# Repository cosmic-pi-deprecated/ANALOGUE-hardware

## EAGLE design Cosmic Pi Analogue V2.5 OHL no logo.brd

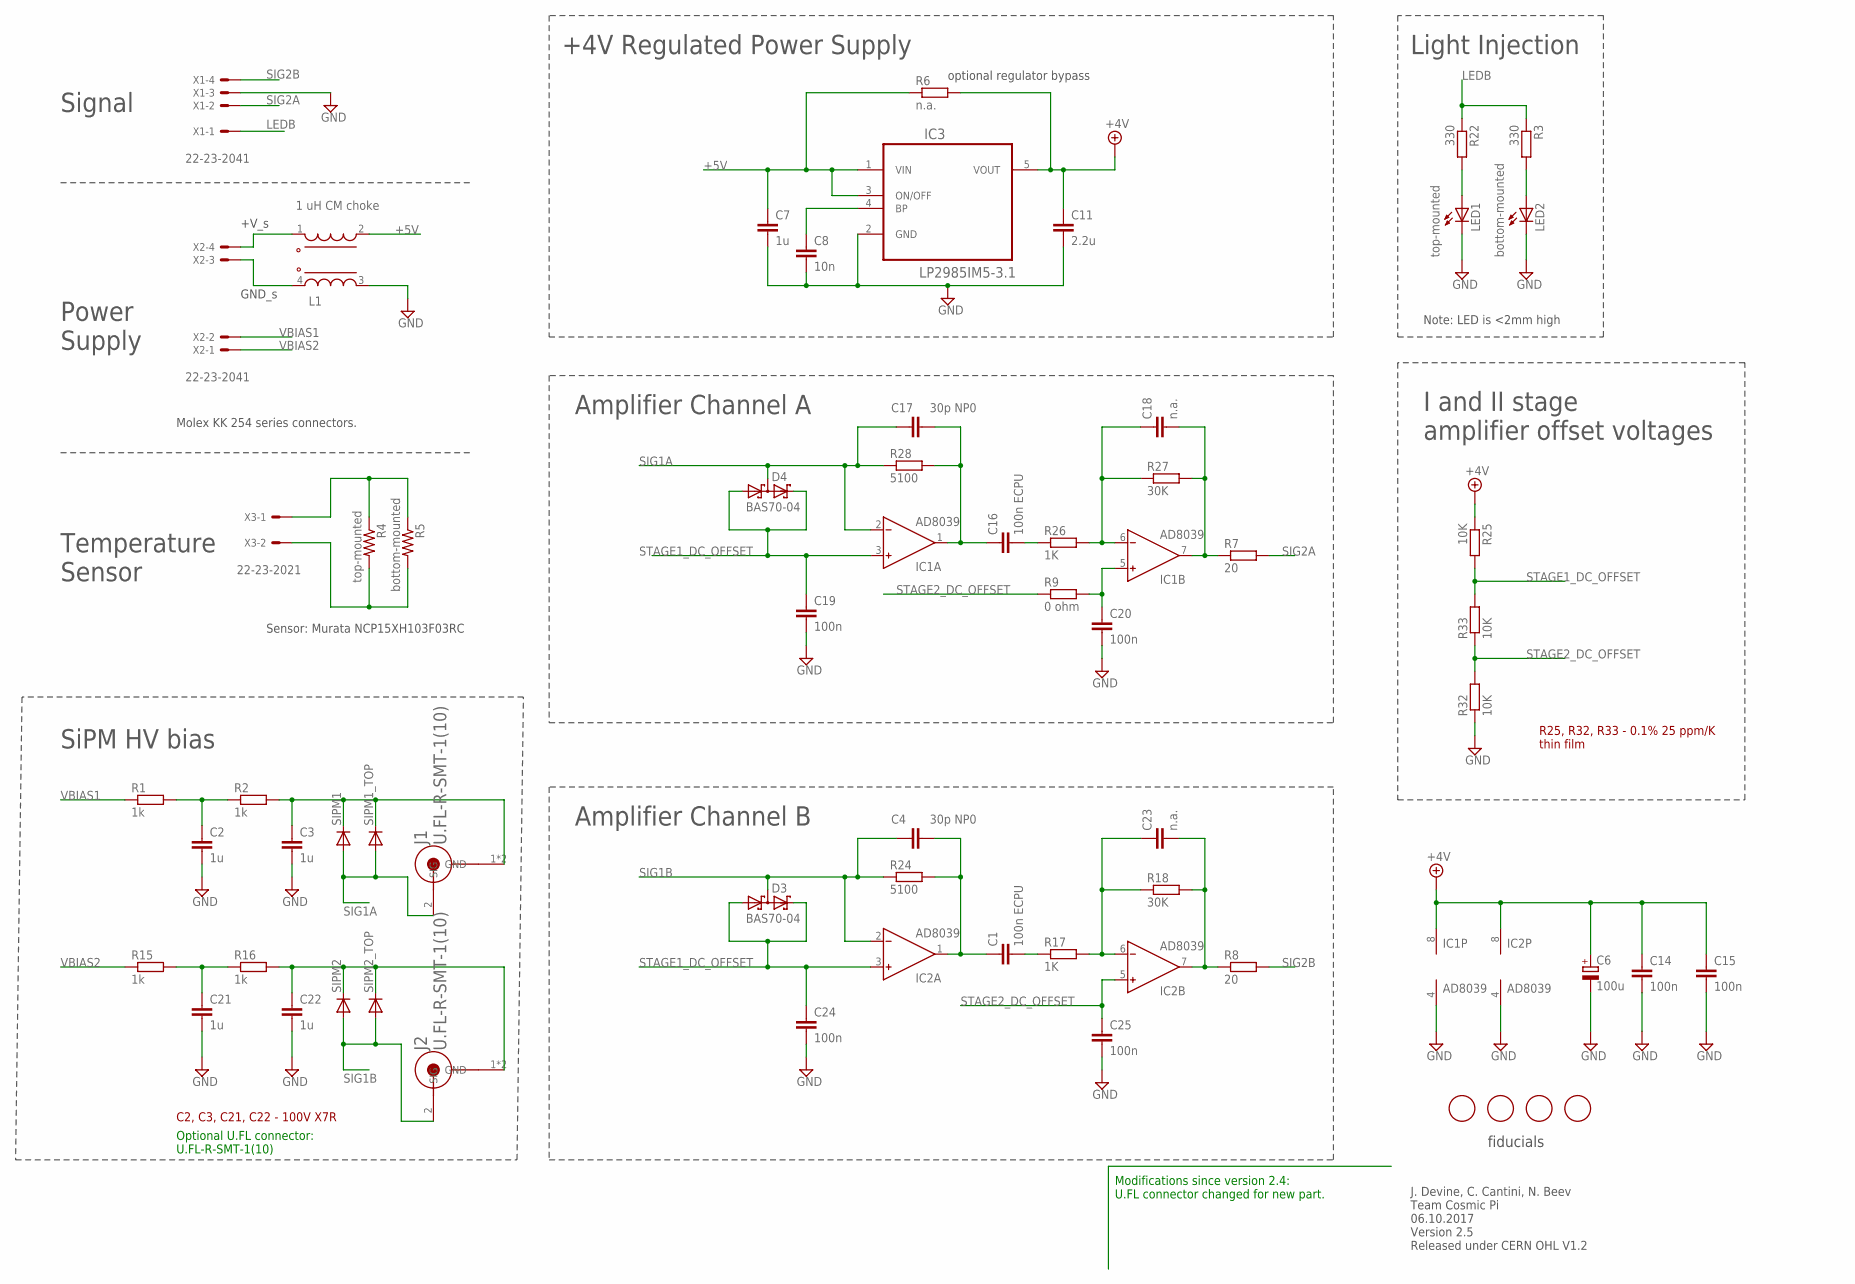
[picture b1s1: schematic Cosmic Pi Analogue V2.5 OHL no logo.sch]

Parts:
C1, C16: 100n ECPU; C0805
C2, C3, C21, C22: 1u; C1206
C4, C17: 30p NP0; C0603
C6: 100u; C/6032-28R
C7: 1u; C0603
C8: 10n; C0603
C11: 2.2u; C0603
C14, C15, C19, C20, C24, C25: 100n; C0603
C18, C23: n.a.; C0603
D3, D4: BAS70-04; SOT23
IC1, IC2: AD8039; SO8
IC3: LP2985IM5-3.1; SOT95P284X120-5N
J1, J2: U.FL-R-SMT-1(10); HRS_U.FL-R-SMT-1(10)
L1: 1 uH CM choke; WE-CNSW_1812
LED1: top-mounted; LED_SML0603
LED2: bottom-mounted; LED_SML0603
R1, R2, R15, R16: 1k; R1206
R3, R22: 330; R0603
R4: top-mounted; R0402
R5: bottom-mounted; R0402
R6: n.a.; R0603
R7, R8: 20; R0603
R9: 0 ohm; R1206
R17, R26: 1K; R0603
R18, R27: 30K; R0603
R24, R28: 5100; R0603
R25, R32, R33: 10K; R0805
SIPM1, SIPM1_TOP, SIPM2, SIPM2_TOP: DIODE-ADVANSID; ASD-NUV3S-P
U$2, U$3, U$4, U$5: FIDUCIAL; FIDUCIAL_1MM
X1, X2: 22-23-2041
X3: 22-23-2021

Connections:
+4V: C6.+, C11.1, C14.1, C15.1, IC1.8 (V+), IC2.8 (V+), IC3.5 (VOUT), R6.2, R25.1
+5V: C7.1, IC3.1 (VIN), IC3.3 (ON/OFF), L1.2 (3), R6.1
GND: C2.2, C3.2, C6.-, C7.2, C8.2, C11.2, C14.2, C15.2, C19.2, C20.2, C21.2, C22.2, C24.2, C25.2, IC1.4 (V-), IC2.4 (V-), IC3.2 (GND), L1.3 (2), LED1.C, LED2.C, R32.1, X1.3
LEDB: R3.1, R22.1, X1.1
unnamed: L1.1 (4), X2.4
unnamed: L1.4 (1), X2.3
unnamed: LED2.A, R3.2
unnamed: C8.1, IC3.4 (BP)
unnamed: C21.1, R15.2, R16.1
unnamed: C18.2, IC1.7 (OUT), R7.1, R27.2
unnamed: C22.1, J2.1 (GND), J2.3 (GND), R16.2, SIPM2.P$1 (C), SIPM2_TOP.P$1 (C)
unnamed: R4.1, R5.1, X3.1
unnamed: C23.2, IC2.7 (OUT), R8.1, R18.2
unnamed: C2.1, R1.2, R2.1
unnamed: R4.2, R5.2, X3.2
unnamed: C20.1, IC1.5 (IN+), R9.2
unnamed: C3.1, J1.1 (GND), J1.3 (GND), R2.2, SIPM1.P$1 (C), SIPM1_TOP.P$1 (C)
unnamed: LED1.A, R22.2
unnamed: C1.1, C4.2, IC2.1 (OUT), R24.2
unnamed: C1.2, R17.1
unnamed: C23.1, IC2.6 (IN-), R17.2, R18.1
unnamed: C16.1, C17.2, IC1.1 (OUT), R28.2
unnamed: C16.2, R26.1
unnamed: C18.1, IC1.6 (IN-), R26.2, R27.1
SIG1A: C17.1, D4.3 (C1A2), IC1.2 (IN-), J1.2 (SIG), R28.1, SIPM1.P$2 (A), SIPM1_TOP.P$2 (A)
SIG1B: C4.1, D3.3 (C1A2), IC2.2 (IN-), J2.2 (SIG), R24.1, SIPM2.P$2 (A), SIPM2_TOP.P$2 (A)
SIG2A: R7.2, X1.2
SIG2B: R8.2, X1.4
STAGE1_DC_OFFSET: C19.1, C24.1, D3.1 (A1), D3.2 (C2), D4.1 (A1), D4.2 (C2), IC1.3 (IN+), IC2.3 (IN+), R25.2, R33.2
STAGE2_DC_OFFSET: C25.1, IC2.5 (IN+), R9.1, R32.2, R33.1
VBIAS1: R1.1, X2.2
VBIAS2: R15.1, X2.1

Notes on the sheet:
J. Devine, C. Cantini, N. Beev Team Cosmic Pi 06.10.2017 Version 2.5 Released under CERN OHL V1.2
Signal
Power Supply
Molex KK 254 series connectors.
Note: LED is <2mm high
+4V Regulated Power Supply
Amplifier Channel A
Amplifier Channel B
SiPM HV bias
Temperature Sensor
optional regulator bypass
+V_s
GND_s
Light Injection
I and II stage amplifier offset voltages
fiducials
Sensor: Murata NCP15XH103F03RC
R25, R32, R33 - 0.1% 25 ppm/K thin film
C2, C3, C21, C22 - 100V X7R
Optional U.FL connector: U.FL-R-SMT-1(10)
Modifications since version 2.4: U.FL connector changed for new part.

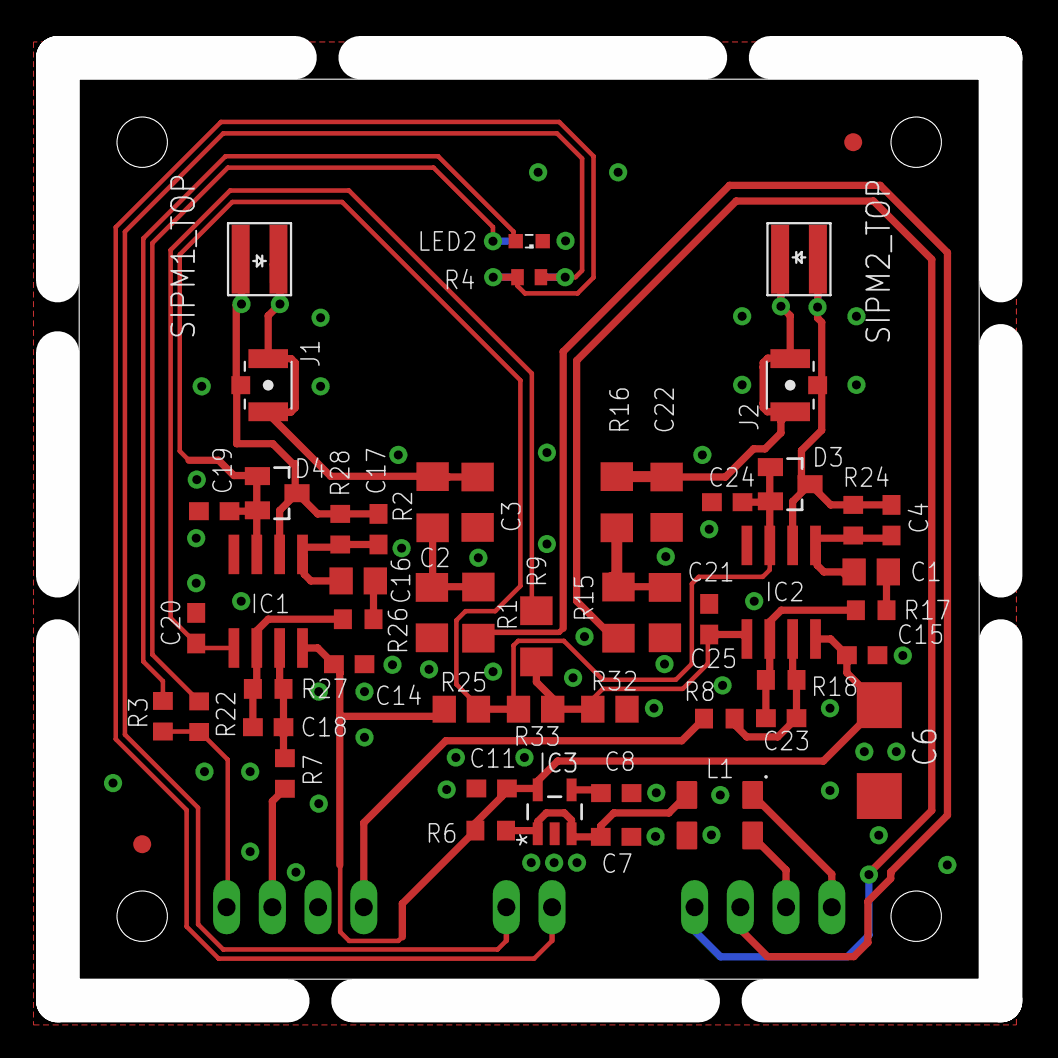
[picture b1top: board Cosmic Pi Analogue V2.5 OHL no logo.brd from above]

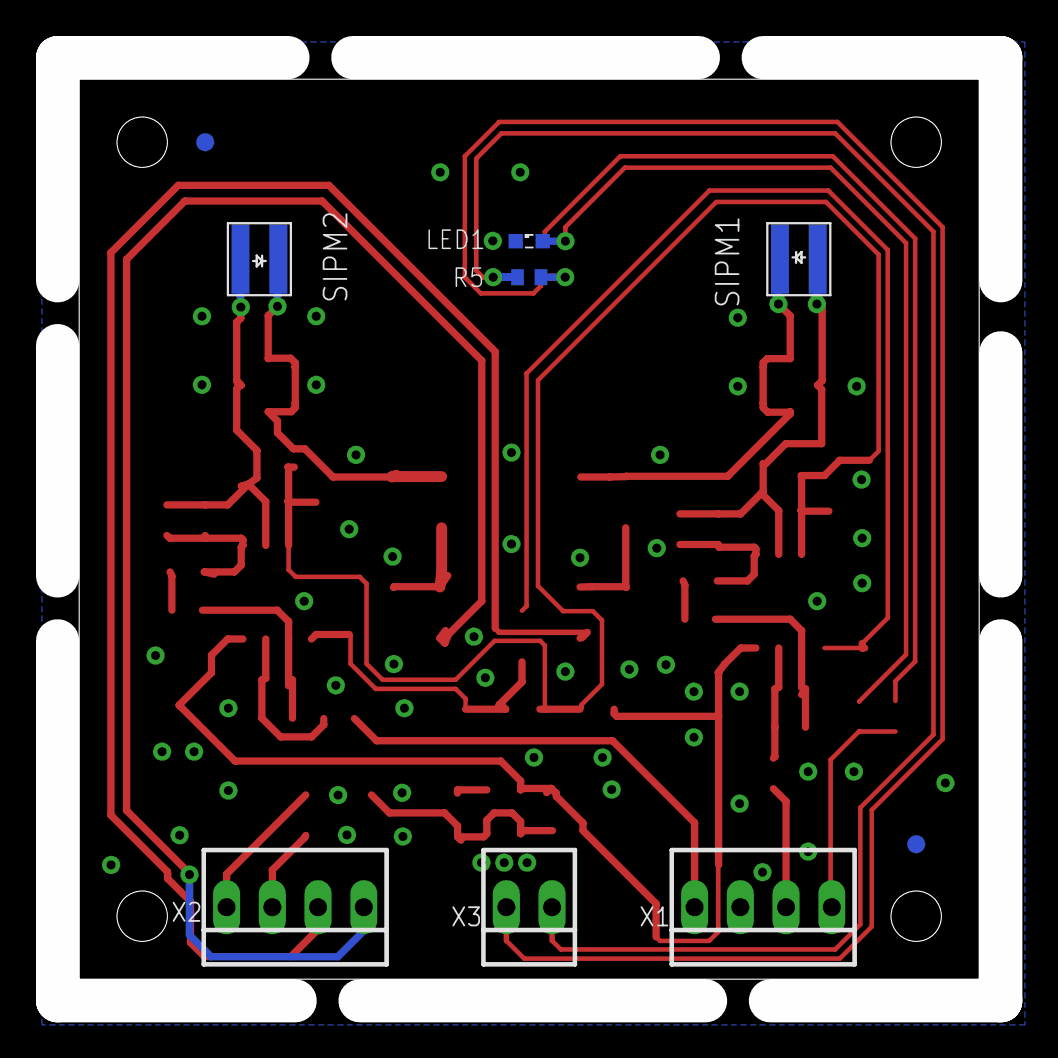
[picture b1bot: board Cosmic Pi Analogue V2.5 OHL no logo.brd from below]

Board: 2 copper layers, 52.4 x 52.4 mm, 62 parts (9 on the bottom side), 32 nets.

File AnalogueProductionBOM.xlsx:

Qty | Value | Parts | Package | Tolerance | Wattage | Voltage Rating, Type | Manufacturer | MPN | Description | Device | Side | Mounting
1 | 0 ohm | R9 | R1206 |  | 1/4W |  |  |  | RESISTOR, European symbol | R-EU_R1206 | Top | SMD
1 | 1 uH CM choke | L1 | WE-CNSW_1812 |  |  |  | Wurth | 744235601 | WE-CNSW SMD Common Mode Line Filter | WE-CNSW_1812_744235601 | Top | SMD
6 | 100n | C14, C15, C19, C20, C24, C25 | C0603 | 0.1 |  | 50V, X7R |  |  | CAPACITOR, European symbol | C-EUC0603 | Top | SMD
2 | 100n ECPU | C1, C16 | C0805 | 0.2 |  | 16V |  |  | CAPACITOR, European symbol | C-EUC0805 | Top | SMD
1 | 100u | C6 | C/6032-28R | 0.1 |  | 10V, Tantalum |  |  | POLARIZED CAPACITOR, European symbol | CPOL-EUC/6032-28R | Top | SMD
3 | 10K | R25, R32, R33 | R0805 | 1E-3 | 125mW |  |  |  | RESISTOR, European symbol | R-EU_R0805 | Top | SMD
1 | 10n | C8 | C0603 | 0.1 |  | 50V, X7R |  |  | CAPACITOR, European symbol | C-EUC0603 | Top | SMD
2 | 1K | R17, R26 | R0603 | 0.01 | 1/10W |  |  |  | RESISTOR, European symbol | R-EU_R0603 | Top | SMD
4 | 1k | R1, R2, R15, R16 | R1206 | 0.01 | 1/4W |  |  |  | RESISTOR, European symbol | R-EU_R1206 | Top | SMD
1 | 1u | C7 | C0603 | 0.1 |  | 25V, X7R |  |  | CAPACITOR, European symbol | C-EUC0603 | Top | SMD
4 | 1u | C2, C3, C21, C22 | C1206 | 0.1 |  | 100V, X7R |  |  | CAPACITOR, European symbol | C-EUC1206 | Top | SMD
1 | 2.2u | C11 | C0603 | 0.1 |  | 10V, X7R |  |  | CAPACITOR, European symbol | C-EUC0603 | Top | SMD
2 | 20 | R7, R8 | R0603 | 0.01 | 1/10W |  |  |  | RESISTOR, European symbol | R-EU_R0603 | Top | SMD
1 | 22-23-2021 | X3 | 22-23-2021 |  |  |  | MOLEX | 22-23-2021 | .100 (2.54mm) Center Header - 2 Pin" | 22-23-2021 | Top | TH
2 | 22-23-2041 | X1, X2 | 22-23-2041 |  |  |  | MOLEX | 22-23-2041 | .100 (2.54mm) Center Header - 4 Pin" | 22-23-2041 | Top | TH
2 | 30K | R18, R27 | R0603 | 0.01 | 1/10W |  |  |  | RESISTOR, European symbol | R-EU_R0603 | Top | SMD
2 | 30p NP0 | C4, C17 | C0603 | 0.05 |  | 50V, NPO |  |  | CAPACITOR, European symbol | C-EUC0603 | Top | SMD
1 | 330 | R22 | R0603 | 0.01 | 1/10W |  |  |  | RESISTOR, European symbol | R-EU_R0603 | Top | SMD
2 | 5100 | R24, R28 | R0603 | 0.01 | 1/8W |  |  |  | RESISTOR, European symbol | R-EU_R0603 | Top | SMD
2 | AD8039 | IC1, IC2 | SO8 |  |  |  | ALTERA CORPORATION | AD8033ARZ | 2.7 V, 800 ?A, 80 MHz Rail-to-Rail I/O Amplifiers | AD8033R | Top | SMD
2 | BAS70-04 | D3, D4 | SOT23 |  |  |  | Vishay | BAS70-04-E3-08 | Silicon Schottky Diodes | BAS70-04 | Top | SMD
1 | LP2985IM5-3.1 | IC3 | SOT95P284X120-5N |  |  |  | Texas Instruments | LP2985IM5-3.3/NOPB | Low-Dropout Regulator | LP2985IM5-3.1 | Top | SMD
2 | U.FL-R-SMT-1(10) | J1, J2 | HRS_U.FL-R-SMT-1(10) |  |  |  | Hirose | U.FL-R-SMT-1(10) | U.FL, Ultra Miniature Coaxial Connector Receptacle, Male Pin 50 Ohm Surface Mou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 | U.FL-R-SMT-1(10) | Top | SMD
1 | top-mounted | LED1 | LED_SML0603 |  |  |  | LTST-S270TBKT-5A |  | 0603 Blue LED | LED_ESML0603 | Top | SMD

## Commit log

2017-09-11 First update
2017-10-26 Version 2.5 production update
2017-10-26 updated license files
2018-01-28 Wrong part number identified and corrected IC1, IC2, IC3 and IC4
    The AD8039 was incorrectly tagged as an AD8033 in the extended description fields and in the BOM spreadsheet. This has now been corrected. Based on production testing, analogue units with the AD8033 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

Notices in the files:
parts and their libraries:
EMCComponents: Copyright: Würth Elektronik
